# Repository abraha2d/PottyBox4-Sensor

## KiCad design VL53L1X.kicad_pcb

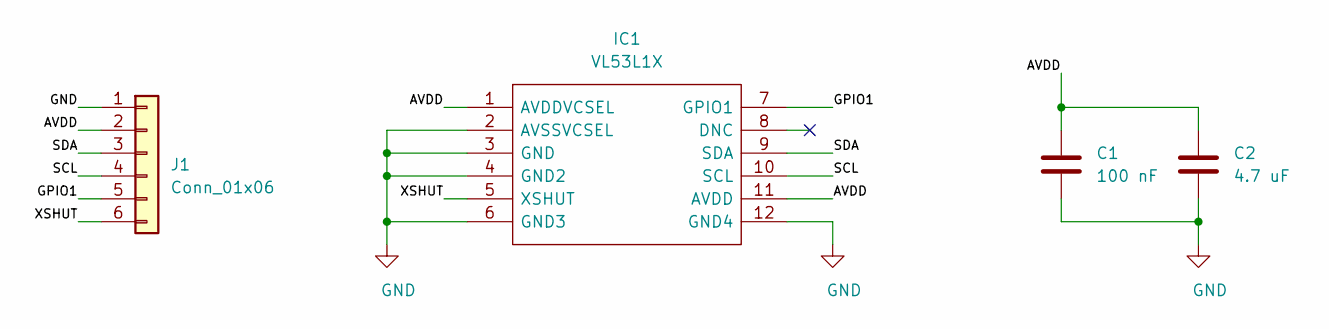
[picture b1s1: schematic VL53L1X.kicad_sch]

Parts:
C1: 100 nF; C_0201_0603Metric_Pad0.64x0.40mm_HandSolder
C2: 4.7 uF; C_0201_0603Metric_Pad0.64x0.40mm_HandSolder
IC1: VL53L1X; Manufacturer_Part_Number VL53L1X
J1: Conn_01x06; JST_SH_SM06B-SRSS-TB_1x06-1MP_P1.00mm_Horizontal

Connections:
/AVDD: C1.1, C2.1, IC1.1 (AVDDVCSEL), IC1.11 (AVDD), J1.2
/GPIO1: IC1.7 (GPIO1), J1.5
/SCL: IC1.10 (SCL), J1.4
/SDA: IC1.9 (SDA), J1.3
/XSHUT: IC1.5 (XSHUT), J1.6
GND: C1.2, C2.2, IC1.2 (AVSSVCSEL), IC1.3 (GND), IC1.4 (GND2), IC1.6 (GND3), IC1.12 (GND4), J1.1

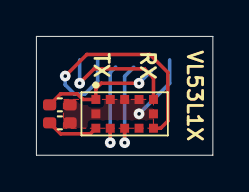
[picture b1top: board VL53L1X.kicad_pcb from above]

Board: 2 copper layers, 9.8 x 6.6 mm, 4 parts (1 on the bottom side), 6 nets.

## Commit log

2020-12-26 Fix paths
2020-12-27 schematic, layout, routing, all done.
2020-12-27 Generate gerbers for JLCPCB
2020-12-27 Specify JLCPCB order number location
2020-12-27 Switch from 0201/0603Metric to 0402 caps
